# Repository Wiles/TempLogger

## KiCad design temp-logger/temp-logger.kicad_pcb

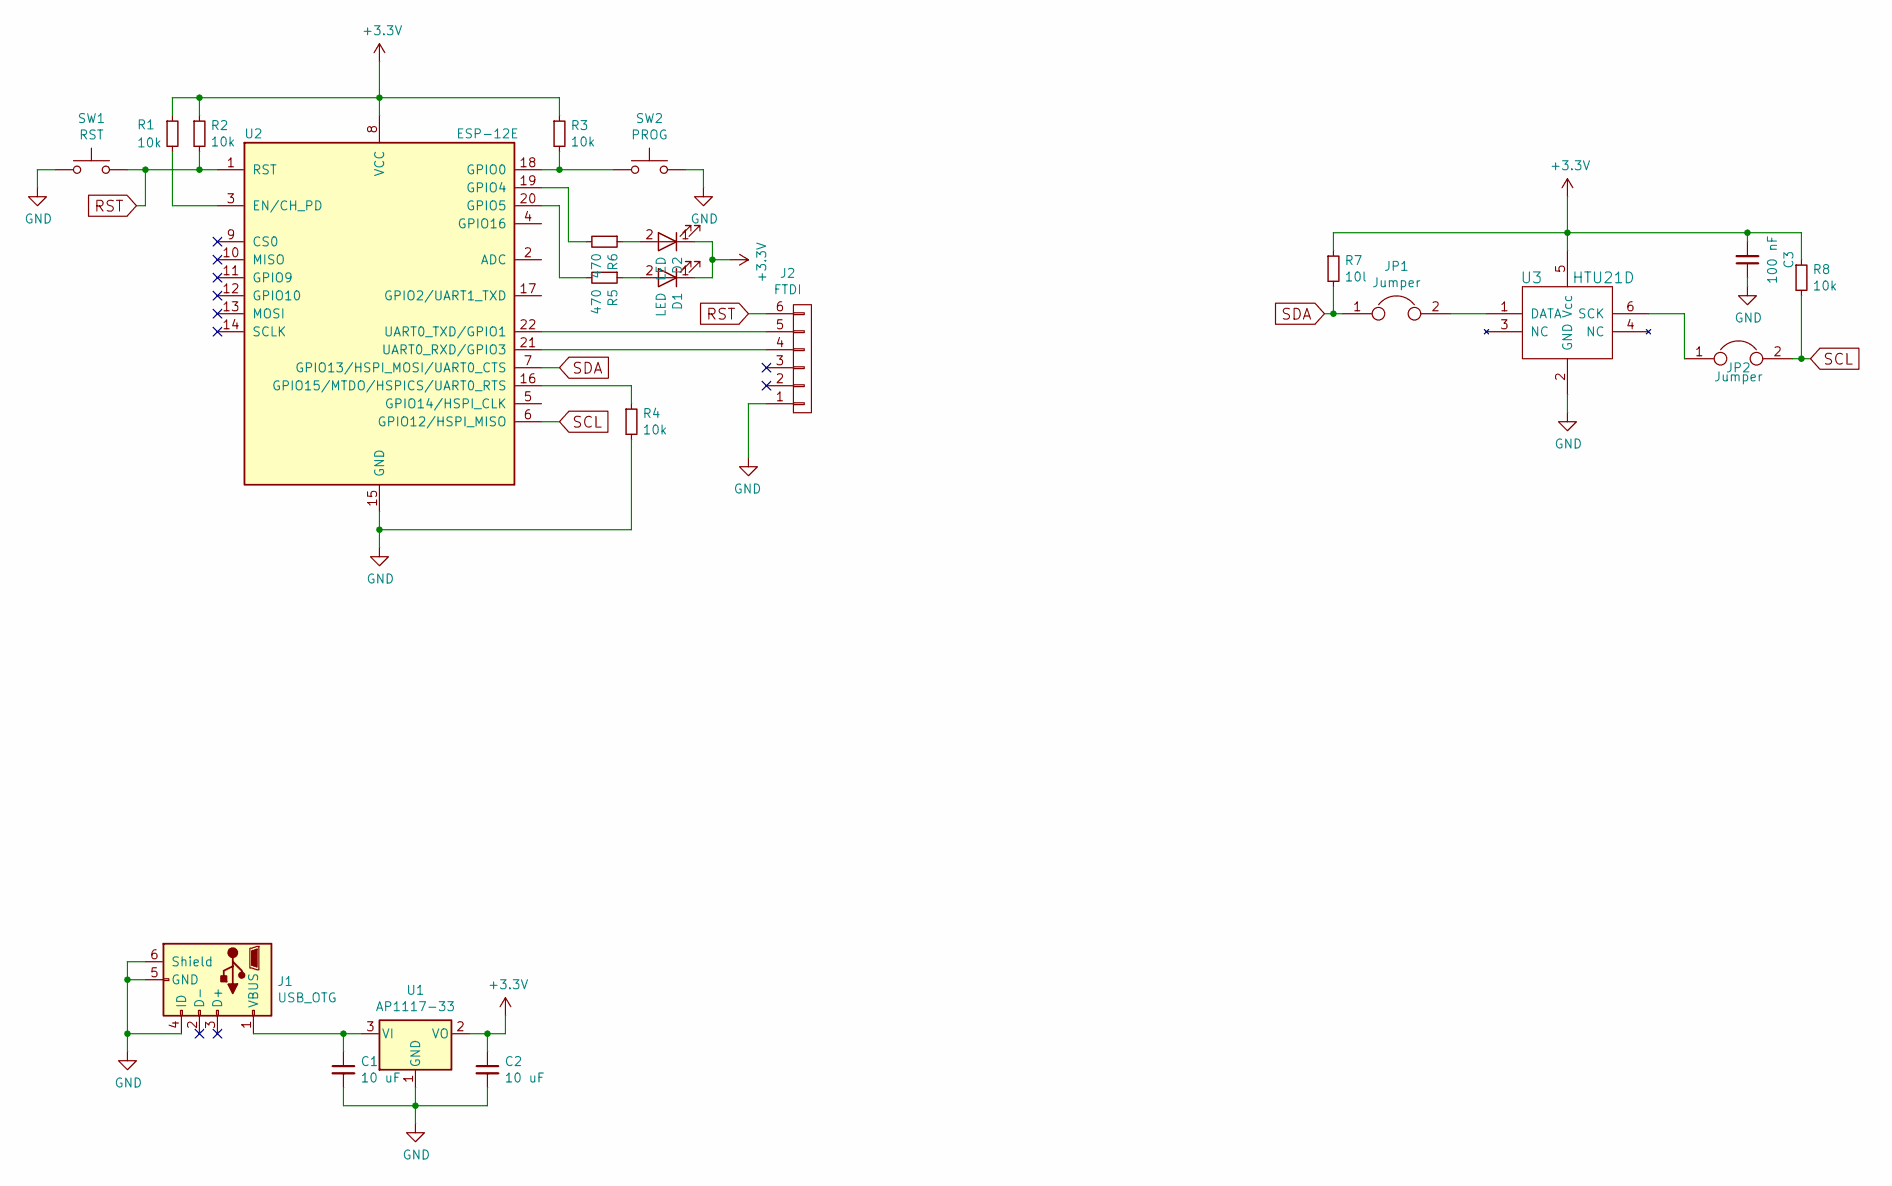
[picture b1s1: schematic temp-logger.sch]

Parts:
C1, C2: 10 uF; C_1206_HandSoldering
C3: 100 nF; C_0603_HandSoldering
D1, D2: LED; LED_1206_HandSoldering
J1: USB_OTG; USB_Micro-B_Molex_47346-0001
J2: FTDI; Pin_Header_Straight_1x06_Pitch2.54mm
JP1, JP2: Jumper; R_0603_HandSoldering
R1, R2, R3, R4, R8: 10k; R_0603_HandSoldering
R5, R6: 470; R_0603_HandSoldering
R7: 10l; R_0603_HandSoldering
SW1: RST; SW_SPST_B3U-1000P
SW2: PROG; SW_SPST_B3U-1000P
U1: AP1117-33; SOT-223
U2: ESP-12E
U3: HTU21D; DFN-6-1EP_3x3mm_Pitch0.95mm

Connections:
+3V3: C2.1, C3.2, D1.1 (K), D2.1 (K), R1.1, R2.1, R3.1, R7.1, R8.1, U1.2 (VO), U2.8 (VCC), U3.5 (Vcc)
GND: C1.2, C2.2, C3.1, J1.4 (ID), J1.5 (GND), J1.6 (Shield), J2.1, R4.2, SW1.1, SW2.2, U1.1 (GND), U2.15 (GND), U3.2 (GND)
unnamed: C1.1, J1.1 (VBUS), U1.3 (VI)
unnamed: D1.2 (A), R5.1
unnamed: D2.2 (A), R6.1
unnamed: J2.4, U2.21 (UART0_RXD/GPIO3)
unnamed: J2.5, U2.22 (UART0_TXD/GPIO1)
unnamed: JP1.2, U3.1 (DATA)
unnamed: JP2.1, U3.6 (SCK)
unnamed: R1.2, U2.3 (EN/CH_PD)
unnamed: R3.2, SW2.1, U2.18 (GPIO0)
unnamed: R4.1, U2.16 (GPIO15/MTDO/HSPICS/UART0_RTS)
unnamed: R5.2, U2.20 (GPIO5)
unnamed: R6.2, U2.19 (GPIO4)
RST: J2.6, R2.2, SW1.2, U2.1 (RST)
SCL: JP2.2, R8.2, U2.6 (GPIO12/HSPI_MISO)
SDA: JP1.1, R7.2, U2.7 (GPIO13/HSPI_MOSI/UART0_CTS)

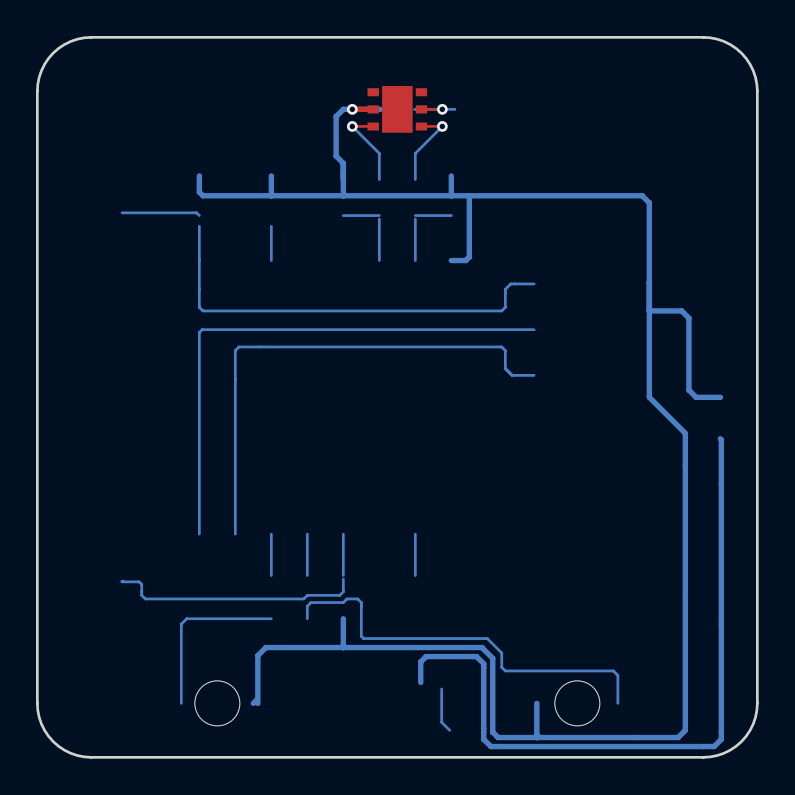
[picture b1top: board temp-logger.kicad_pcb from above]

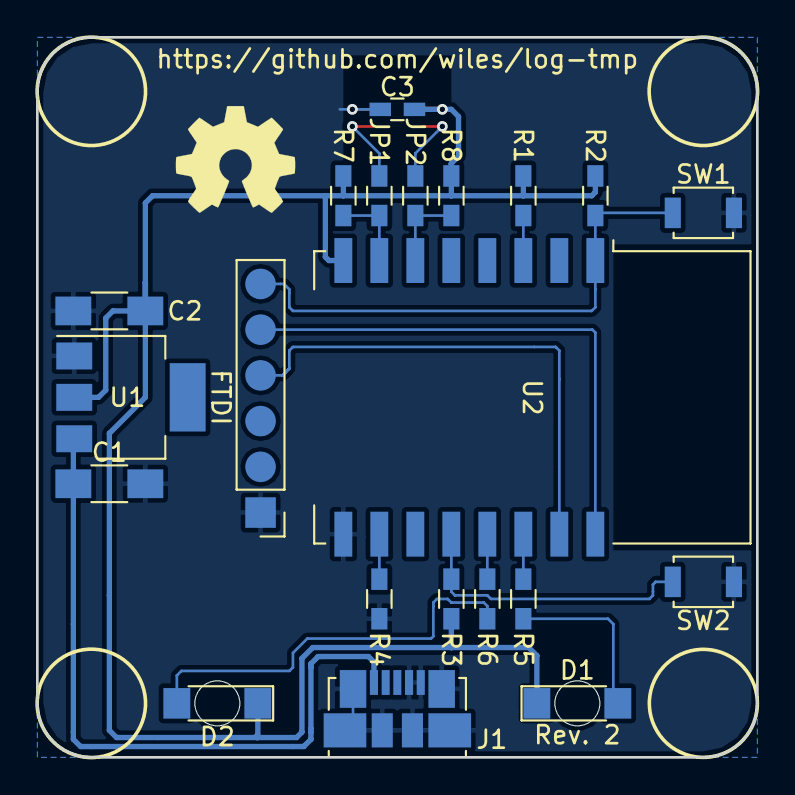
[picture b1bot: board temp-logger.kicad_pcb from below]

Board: 2 copper layers, 40.0 x 40.0 mm, 22 parts (21 on the bottom side), 17 nets.

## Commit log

2016-03-27 Added switch to re-enter WIFI manager
    - Avoided use of startConfigPortal as it caused issues with the Thingspeak parameter
2016-03-28 Added status light for when Wifi configuration is required
2016-07-31 Humidex calculation
2017-11-12 Squashed 'temp-logger/libraries/esp8266/' content from commit 86f494d
    git-subtree-dir: temp-logger/libraries/esp8266
    git-subtree-split: 86f494d5fc7172b21e8d7a327fc2c826f29cc395
2017-11-12 Start of redesign using HTU21D and compatible chips
2017-11-13 Hooked up LEDs
2017-11-13 Fixed R6 label location
2018-01-15 Updated code to use HDC1080
2018-01-15 Renamed ino file to match new project name.
2018-01-15 Redid layout to make soldering and programming easier
